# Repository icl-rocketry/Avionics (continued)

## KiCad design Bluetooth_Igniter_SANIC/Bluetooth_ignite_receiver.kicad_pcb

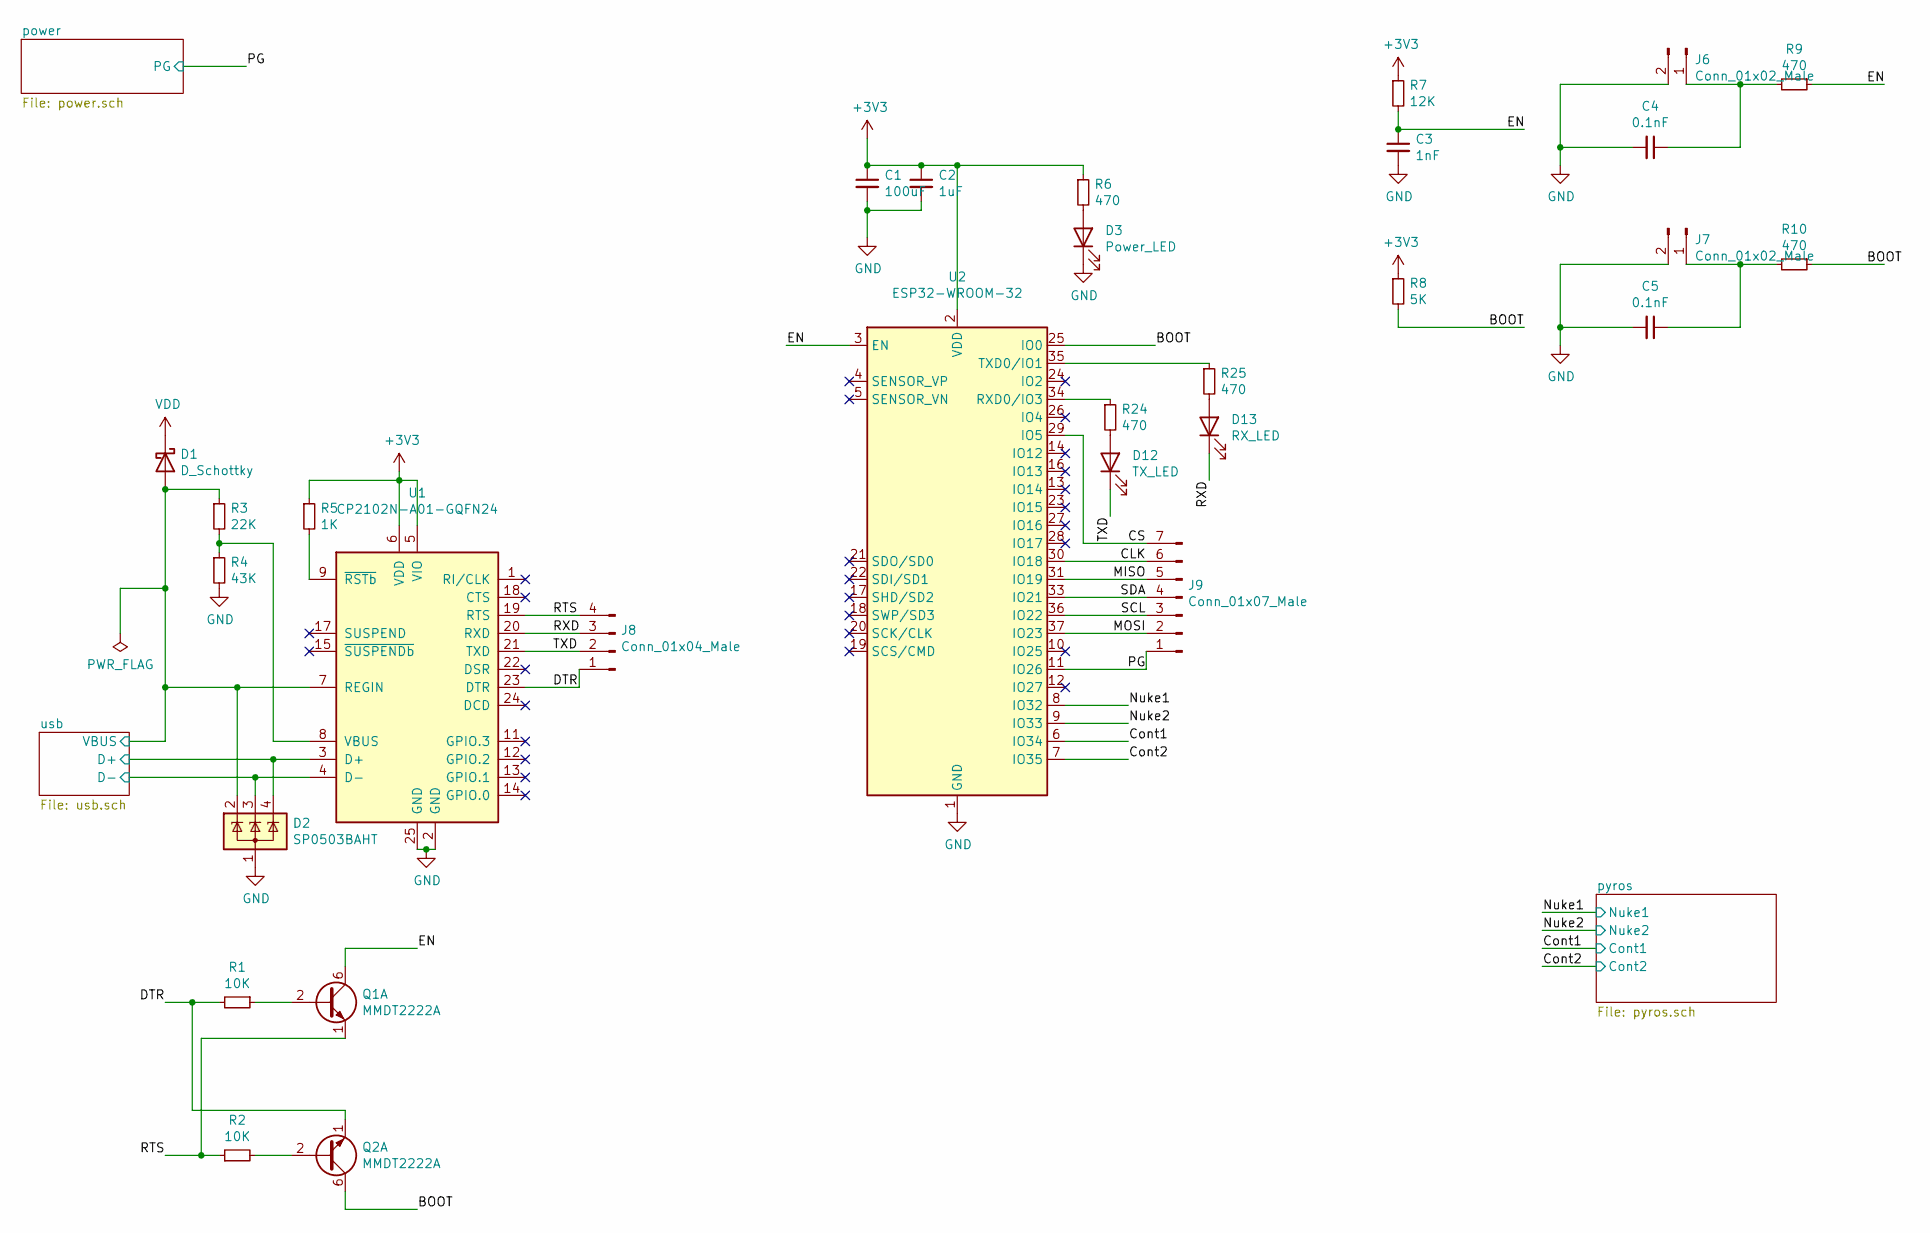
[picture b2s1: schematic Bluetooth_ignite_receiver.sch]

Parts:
C1: 100uF; C_0603_1608Metric
C2: 1uF; C_0603_1608Metric
C3: 1nF; C_0603_1608Metric
C4, C5: 0.1nF; C_0603_1608Metric
D1: D_Schottky; D_SOD-123F
D2: SP0503BAHT; SOT-143
D3: Power_LED; LED_0603_1608Metric_Castellated
D12: TX_LED; LED_0603_1608Metric_Castellated
D13: RX_LED; LED_0603_1608Metric_Castellated
J6, J7: Conn_01x02_Male; PinHeader_1x02_P2.54mm_Vertical
J8: Conn_01x04_Male; PinHeader_1x04_P2.54mm_Vertical
J9: Conn_01x07_Male; PinHeader_1x07_P2.54mm_Vertical
Q1, Q2: MMDT2222A; SOT-363_SC-70-6
R1, R2: 10K; R_0603_1608Metric
R3: 22K; R_0603_1608Metric
R4: 43K; R_0603_1608Metric
R5: 1K; R_0603_1608Metric
R6, R9, R10, R24, R25: 470; R_0603_1608Metric
R7: 12K; R_0603_1608Metric
R8: 5K; R_0603_1608Metric
U1: CP2102N-A01-GQFN24; QFN-24-1EP_4x4mm_P0.5mm_EP2.6x2.6mm
U2: ESP32-WROOM-32

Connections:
+3V3: C1.1, C2.1, R5.1, R6.1, R7.1, R8.1, U1.5 (VIO), U1.6 (VDD), U2.2 (VDD); also elsewhere on the board
/BOOT: Q2.6 (C1), R8.2, R10.1, U2.25 (IO0)
/CLK: J9.6, U2.30 (IO18)
/CS: J9.7, U2.29 (IO5)
/Cont1: U2.6 (IO34); also elsewhere on the board
/Cont2: U2.7 (IO35); also elsewhere on the board
/DTR: J8.1, Q2.1 (E1), R1.2, U1.23 (DTR)
/EN: C3.1, Q1.6 (C1), R7.2, R9.1, U2.3 (EN)
/MISO: J9.5, U2.31 (IO19)
/MOSI: J9.2, U2.37 (IO23)
/Nuke1: U2.8 (IO32); also elsewhere on the board
/Nuke2: U2.9 (IO33); also elsewhere on the board
/PG: J9.1, U2.11 (IO26); also elsewhere on the board
/RTS: J8.4, Q1.1 (E1), R2.1, U1.19 (RTS)
/RXD: D13.1 (K), J8.3, U1.20 (RXD)
/SCL: J9.3, U2.36 (IO22)
/SDA: J9.4, U2.33 (IO21)
/TXD: D12.1 (K), J8.2, U1.21 (TXD)
/usb/D+: D2.4 (K), U1.3 (D+); also elsewhere on the board
/usb/D-: D2.3 (K), U1.4 (D-); also elsewhere on the board
/usb/VBUS: D1.2 (A), D2.2 (K), R3.1, U1.7 (REGIN); also elsewhere on the board
GND: C1.2, C2.2, C3.2, C4.2, C5.2, D2.1 (A), D3.1 (K), J6.2, J7.2, R4.2, U1.2 (GND), U1.25 (GND), U2.1 (GND), U2.15 (GND), U2.38 (GND), U2.39 (GND); also elsewhere on the board
unnamed: C4.1, J6.1, R9.2
unnamed: C5.1, J7.1, R10.2
unnamed: D3.2 (A), R6.2
unnamed: D12.2 (A), R24.2
unnamed: D13.2 (A), R25.2
unnamed: Q1.2 (B1), R1.1
unnamed: Q2.2 (B1), R2.2
unnamed: R3.2, R4.1, U1.8 (VBUS)
unnamed: R5.2, U1.9 (~RSTb)
unnamed: R24.1, U2.34 (RXD0/IO3)
unnamed: R25.1, U2.35 (TXD0/IO1)
VDD: D1.1 (K); also elsewhere on the board

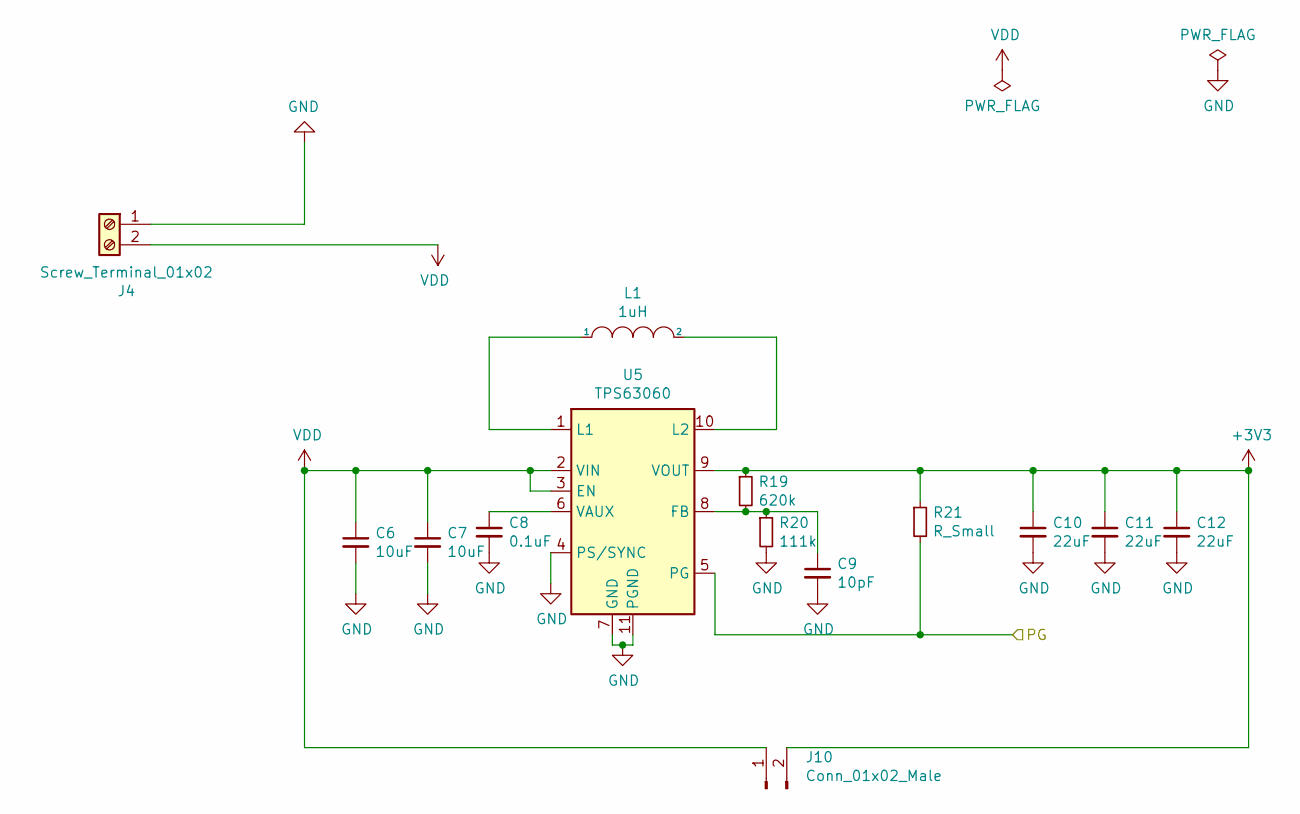
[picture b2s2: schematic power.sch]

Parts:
C6, C7: 10uF; C_0603_1608Metric
C8: 0.1uF; C_0603_1608Metric
C9: 10pF; C_0603_1608Metric
C10, C11, C12: 22uF; C_0603_1608Metric
J4: Screw_Terminal_01x02; TerminalBlock_Phoenix_PT-1,5-2-5.0-H_1x02_P5.00mm_Horizontal
J10: Conn_01x02_Male; PinHeader_1x02_P2.54mm_Vertical
L1: 1uH; L_Taiyo-Yuden_NR-30xx
R19: 620k; R_0603_1608Metric
R20: 111k; R_0603_1608Metric
R21: R_Small; R_0603_1608Metric
U5: TPS63060; Texas_S-PWSON-N10_ThermalVias

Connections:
+3V3: C10.1, C11.1, C12.1, J10.2, R19.1, R21.1, U5.9 (VOUT); also elsewhere on the board
/PG: R21.2, U5.5 (PG); also elsewhere on the board
GND: C6.2, C7.2, C8.2, C9.2, C10.2, C11.2, C12.2, J4.1, R20.2, U5.4 (PS/SYNC), U5.7 (GND), U5.11 (PGND); also elsewhere on the board
unnamed: C8.1, U5.6 (VAUX)
unnamed: C9.1, R19.2, R20.1, U5.8 (FB)
unnamed: L1.1, U5.1 (L1)
unnamed: L1.2, U5.10 (L2)
VDD: C6.1, C7.1, J4.2, J10.1, U5.2 (VIN), U5.3 (EN); also elsewhere on the board

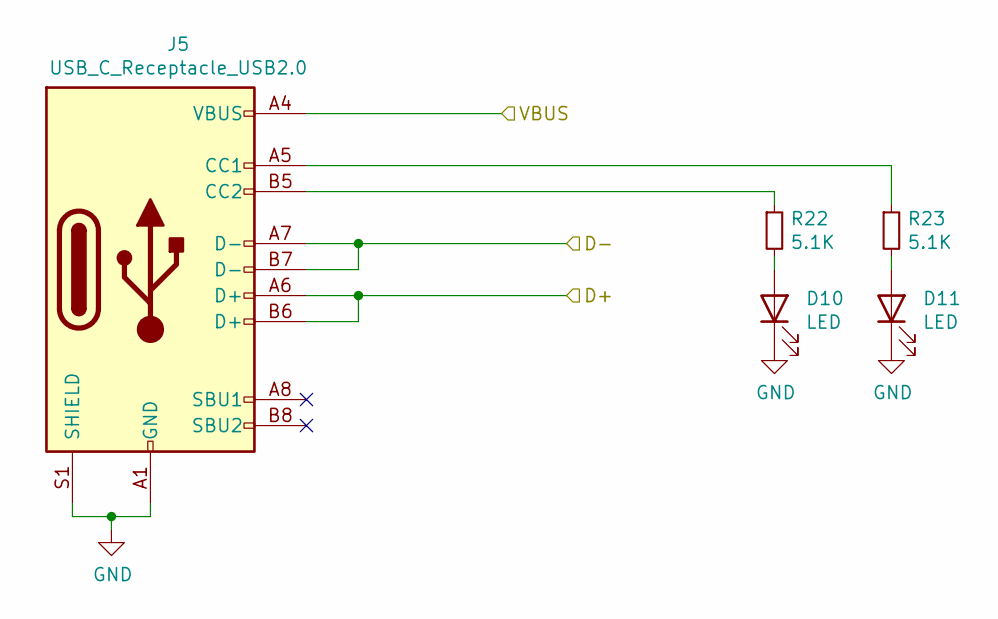
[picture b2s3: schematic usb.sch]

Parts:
D10, D11: LED; LED_0603_1608Metric_Castellated
J5: USB_C_Receptacle_USB2.0; USB_C_Receptacle_XKB_U262-16XN-4BVC11
R22, R23: 5.1K; R_0603_1608Metric

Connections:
/usb/D+: J5.A6 (D+), J5.B6 (D+); also elsewhere on the board
/usb/D-: J5.A7 (D-), J5.B7 (D-); also elsewhere on the board
/usb/VBUS: J5.A4 (VBUS), J5.A9 (VBUS), J5.B4 (VBUS), J5.B9 (VBUS); also elsewhere on the board
GND: D10.1 (K), D11.1 (K), J5.A1 (GND), J5.A12 (GND), J5.B1 (GND), J5.B12 (GND), J5.S1 (SHIELD); also elsewhere on the board
unnamed: D10.2 (A), R22.2
unnamed: D11.2 (A), R23.2
unnamed: J5.A5 (CC1), R23.1
unnamed: J5.B5 (CC2), R22.1

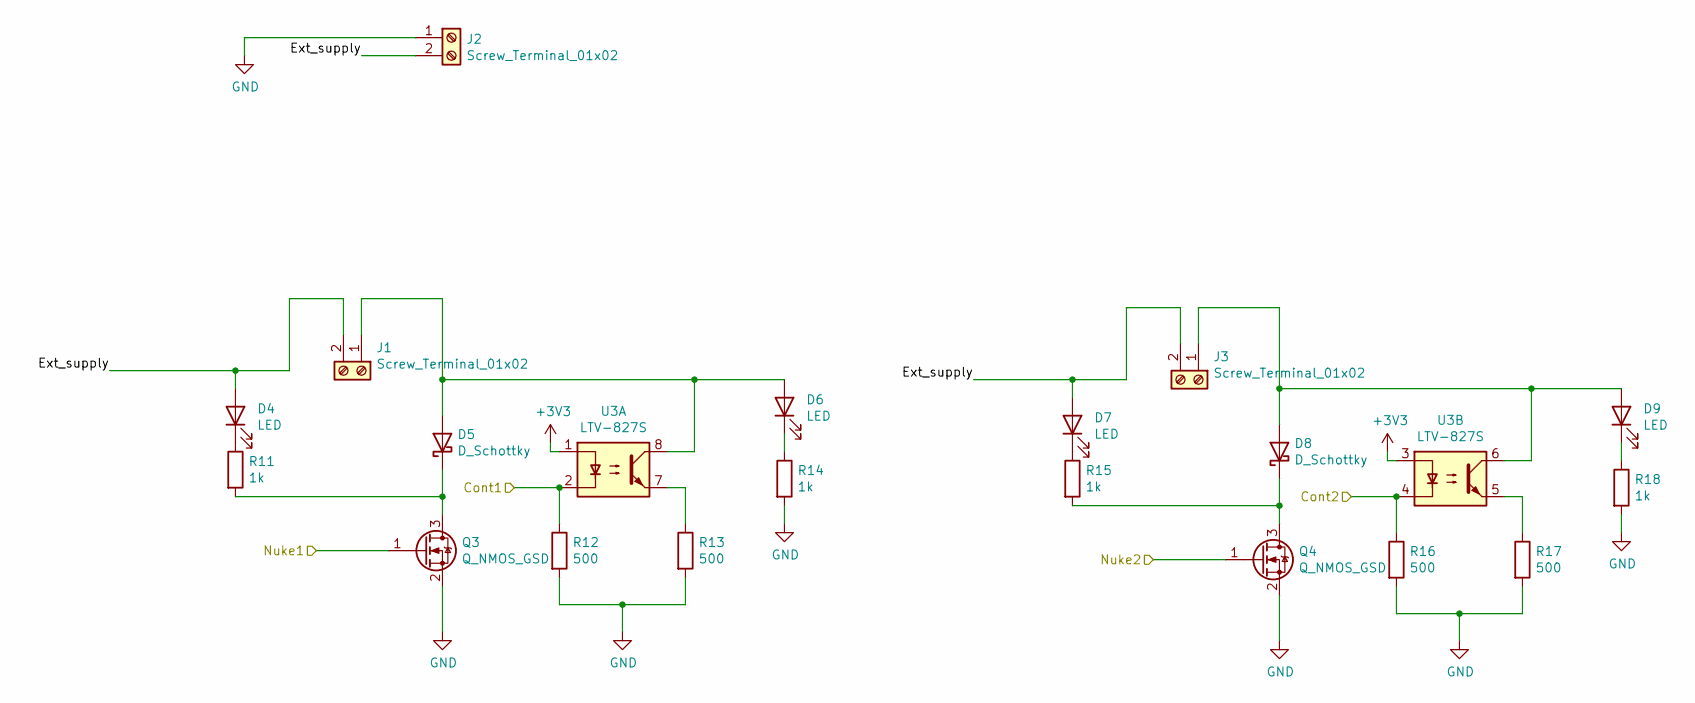
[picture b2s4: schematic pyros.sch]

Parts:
D4, D6, D7, D9: LED; LED_0603_1608Metric_Castellated
D5, D8: D_Schottky; D_SOD-123F
J1, J2, J3: Screw_Terminal_01x02; TerminalBlock_Phoenix_PT-1,5-2-5.0-H_1x02_P5.00mm_Horizontal
Q3, Q4: Q_NMOS_GSD; SOT-23
R11, R14, R15, R18: 1k; R_0603_1608Metric
R12, R13, R16, R17: 500; R_0603_1608Metric
U3: LTV-827S; SMDIP-8_W9.53mm

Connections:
+3V3: U3.1, U3.3; also elsewhere on the board
/Cont1: R12.1, U3.2; also elsewhere on the board
/Cont2: R16.1, U3.4; also elsewhere on the board
/Nuke1: Q3.1 (G); also elsewhere on the board
/Nuke2: Q4.1 (G); also elsewhere on the board
/pyros/Ext_supply: D4.2 (A), D7.2 (A), J1.2, J2.2, J3.2
GND: J2.1, Q3.2 (S), Q4.2 (S), R12.2, R13.2, R14.2, R16.2, R17.2, R18.2; also elsewhere on the board
unnamed: D4.1 (K), R11.1
unnamed: D5.1 (K), Q3.3 (D), R11.2
unnamed: D5.2 (A), D6.2 (A), J1.1, U3.8
unnamed: D6.1 (K), R14.1
unnamed: D7.1 (K), R15.1
unnamed: D8.1 (K), Q4.3 (D), R15.2
unnamed: D8.2 (A), D9.2 (A), J3.1, U3.6
unnamed: D9.1 (K), R18.1
unnamed: R13.1, U3.7
unnamed: R17.1, U3.5

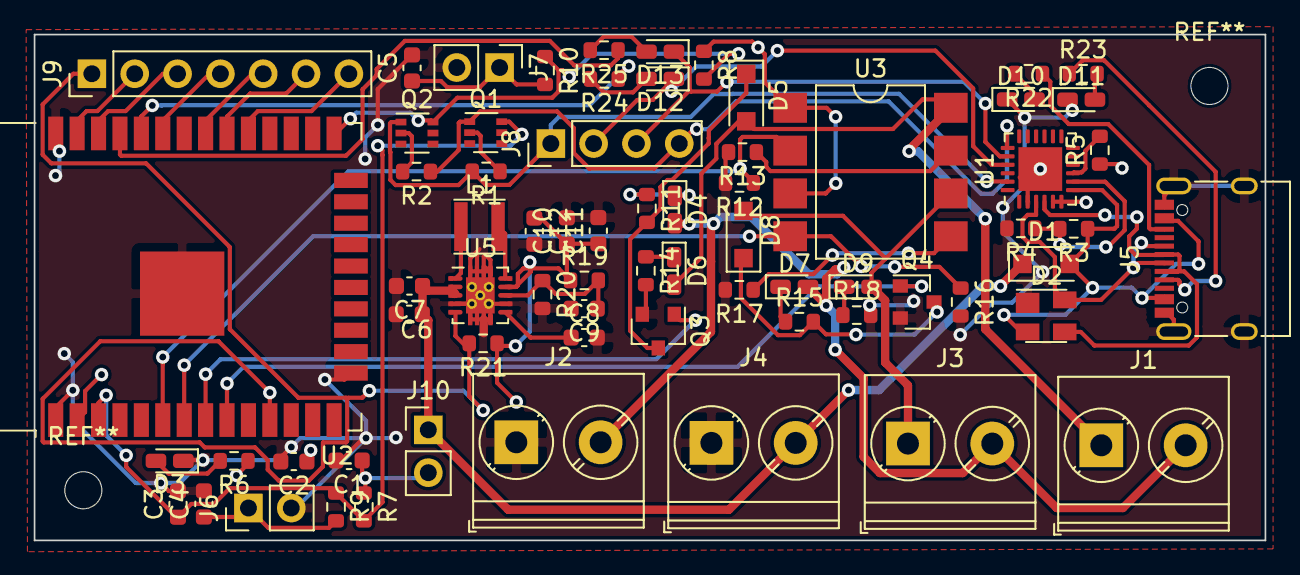
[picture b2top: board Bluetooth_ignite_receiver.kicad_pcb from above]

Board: 2 copper layers, 73.0 x 30.0 mm, 69 parts (0 on the bottom side), 53 nets.

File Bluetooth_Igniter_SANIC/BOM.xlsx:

Reference | Quantity | Value | Footprint | MPN | Price($) | Total Price | Link
C1 | 1 | 100uF | Capacitor_SMD:C_0603_1608Metric | TAJB107K006RNJ | 0.20519999999999999 | 0.20519999999999999 | https://jlcpcb.com/parts/componentSearch?isFirstLevel=true&f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
C10 C11 C12 | 3 | 22uF | Capacitor_SMD:C_0603_1608Metric | CL21A226MQQNNNE | 2.1399999999999999E-2 | 6.4199999999999993E-2 | https://jlcpcb.com/parts/componentSearch?isFirstLevel=true&f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
C2 | 1 | 1uF | Capacitor_SMD:C_0603_1608Metric | CL05A105KP5NNNC | 5.7000000000000002E-3 | 5.7000000000000002E-3 | https://jlcpcb.com/parts/componentSearch?isFirstLevel=true&f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
C3 C4 C5 | 3 | 1nF | Capacitor_SMD:C_0603_1608Metric | CL21B102KBCNNNC | 1.09E-2 | 3.27E-2 | https://jlcpcb.com/parts/componentSearch?isFirstLevel=true&f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
C6 C7 | 2 | 10uF | Capacitor_SMD:C_0603_1608Metric | CL05A106MQ5NUNC | 1.2200000000000001E-2 | 2.4400000000000002E-2 | https://jlcpcb.com/parts/componentSearch?isFirstLevel=true&f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
C8 | 1 | 0.1uF | Capacitor_SMD:C_0603_1608Metric |  |  | 0
C9 | 1 | 10pF | Capacitor_SMD:C_0603_1608Metric |  |  | 0
D1 D5 D8 | 3 | D_Schottky | Diode_SMD:D_SOD-123F |  |  | 0
D4 D6 D7 D9 D10 D11 | 6 | LED | LED_SMD:LED_0603_1608Metric_Castellated |  |  | 0
D12 | 1 | TX_LED | LED_SMD:LED_0603_1608Metric_Castellated |  |  | 0
D13 | 1 | RX_LED | LED_SMD:LED_0603_1608Metric_Castellated |  |  | 0
D2 | 1 | SP0503BAHT | Package_TO_SOT_SMD:SOT-143 |  |  | 0
D3 | 1 | Power_LED | LED_SMD:LED_0603_1608Metric_Castellated |  |  | 0
J1 J2 J3 J4 | 4 | Screw_Terminal_01x02 | TerminalBlock_Phoenix:TerminalBlock_Phoenix_PT-1,5-2-5.0-H_1x02_P5.00mm_Horizon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 |  |  | 0
J5 | 1 | USB_C_Receptacle_USB2.0 | Connector_USB:USB_C_Receptacle_XKB_U262-16XN-4BVC11 |  |  | 0
J6 J7 J10 | 3 | Conn_01x02_Male | Connector_PinHeader_2.54mm:PinHeader_1x02_P2.54mm_Vertical |  |  | 0
J8 | 1 | Conn_01x04_Male | Connector_PinHeader_2.54mm:PinHeader_1x04_P2.54mm_Vertical |  |  | 0
J9 | 1 | Conn_01x07_Male | Connector_PinHeader_2.54mm:PinHeader_1x07_P2.54mm_Vertical |  |  | 0
L1 | 1 | 1uH | Inductor_SMD:L_Taiyo-Yuden_NR-30xx |  |  | 0
Q1 Q2 | 2 | MMDT2222A | Package_TO_SOT_SMD:SOT-363_SC-70-6 |  |  | 0
Q3 Q4 | 2 | Q_NMOS_GSD | Package_TO_SOT_SMD:SOT-23 |  |  | 0
R1 R2 | 2 | 10K | Resistor_SMD:R_0603_1608Metric |  |  | 0
R11 R14 R15 R18 | 4 | 1k | Resistor_SMD:R_0603_1608Metric |  |  | 0
R12 R13 R16 R17 | 4 | 500 | Resistor_SMD:R_0603_1608Metric |  |  | 0
R19 | 1 | 620k | Resistor_SMD:R_0603_1608Metric |  |  | 0
R20 | 1 | 111k | Resistor_SMD:R_0603_1608Metric |  |  | 0
R21 | 1 | R_Small | Resistor_SMD:R_0603_1608Metric |  |  | 0
R22 R23 | 2 | 5.1K | Resistor_SMD:R_0603_1608Metric |  |  | 0
R3 | 1 | 22K | Resistor_SMD:R_0603_1608Metric |  |  | 0
R4 | 1 | 43K | Resistor_SMD:R_0603_1608Metric |  |  | 0
R5 | 1 | 1K | Resistor_SMD:R_0603_1608Metric |  |  | 0
R6 R9 R10 R24 R25 | 5 | 470 | Resistor_SMD:R_0603_1608Metric |  |  | 0
R7 | 1 | 12K | Resistor_SMD:R_0603_1608Metric |  |  | 0
R8 | 1 | 5K | Resistor_SMD:R_0603_1608Metric |  |  | 0
U1 | 1 | CP2102N-A01-GQFN24 | Package_DFN_QFN:QFN-24-1EP_4x4mm_P0.5mm_EP2.6x2.6mm |  |  | 0
U2 | 1 | ESP32-WROOM-32 | RF_Module:ESP32-WROOM-32 |  |  | 0
U3 | 1 | LTV-827S | Package_DIP:SMDIP-8_W9.53mm |  |  | 0
U5 | 1 | TPS63060 | Package_SON:Texas_S-PWSON-N10_ThermalVias |  |  | 0

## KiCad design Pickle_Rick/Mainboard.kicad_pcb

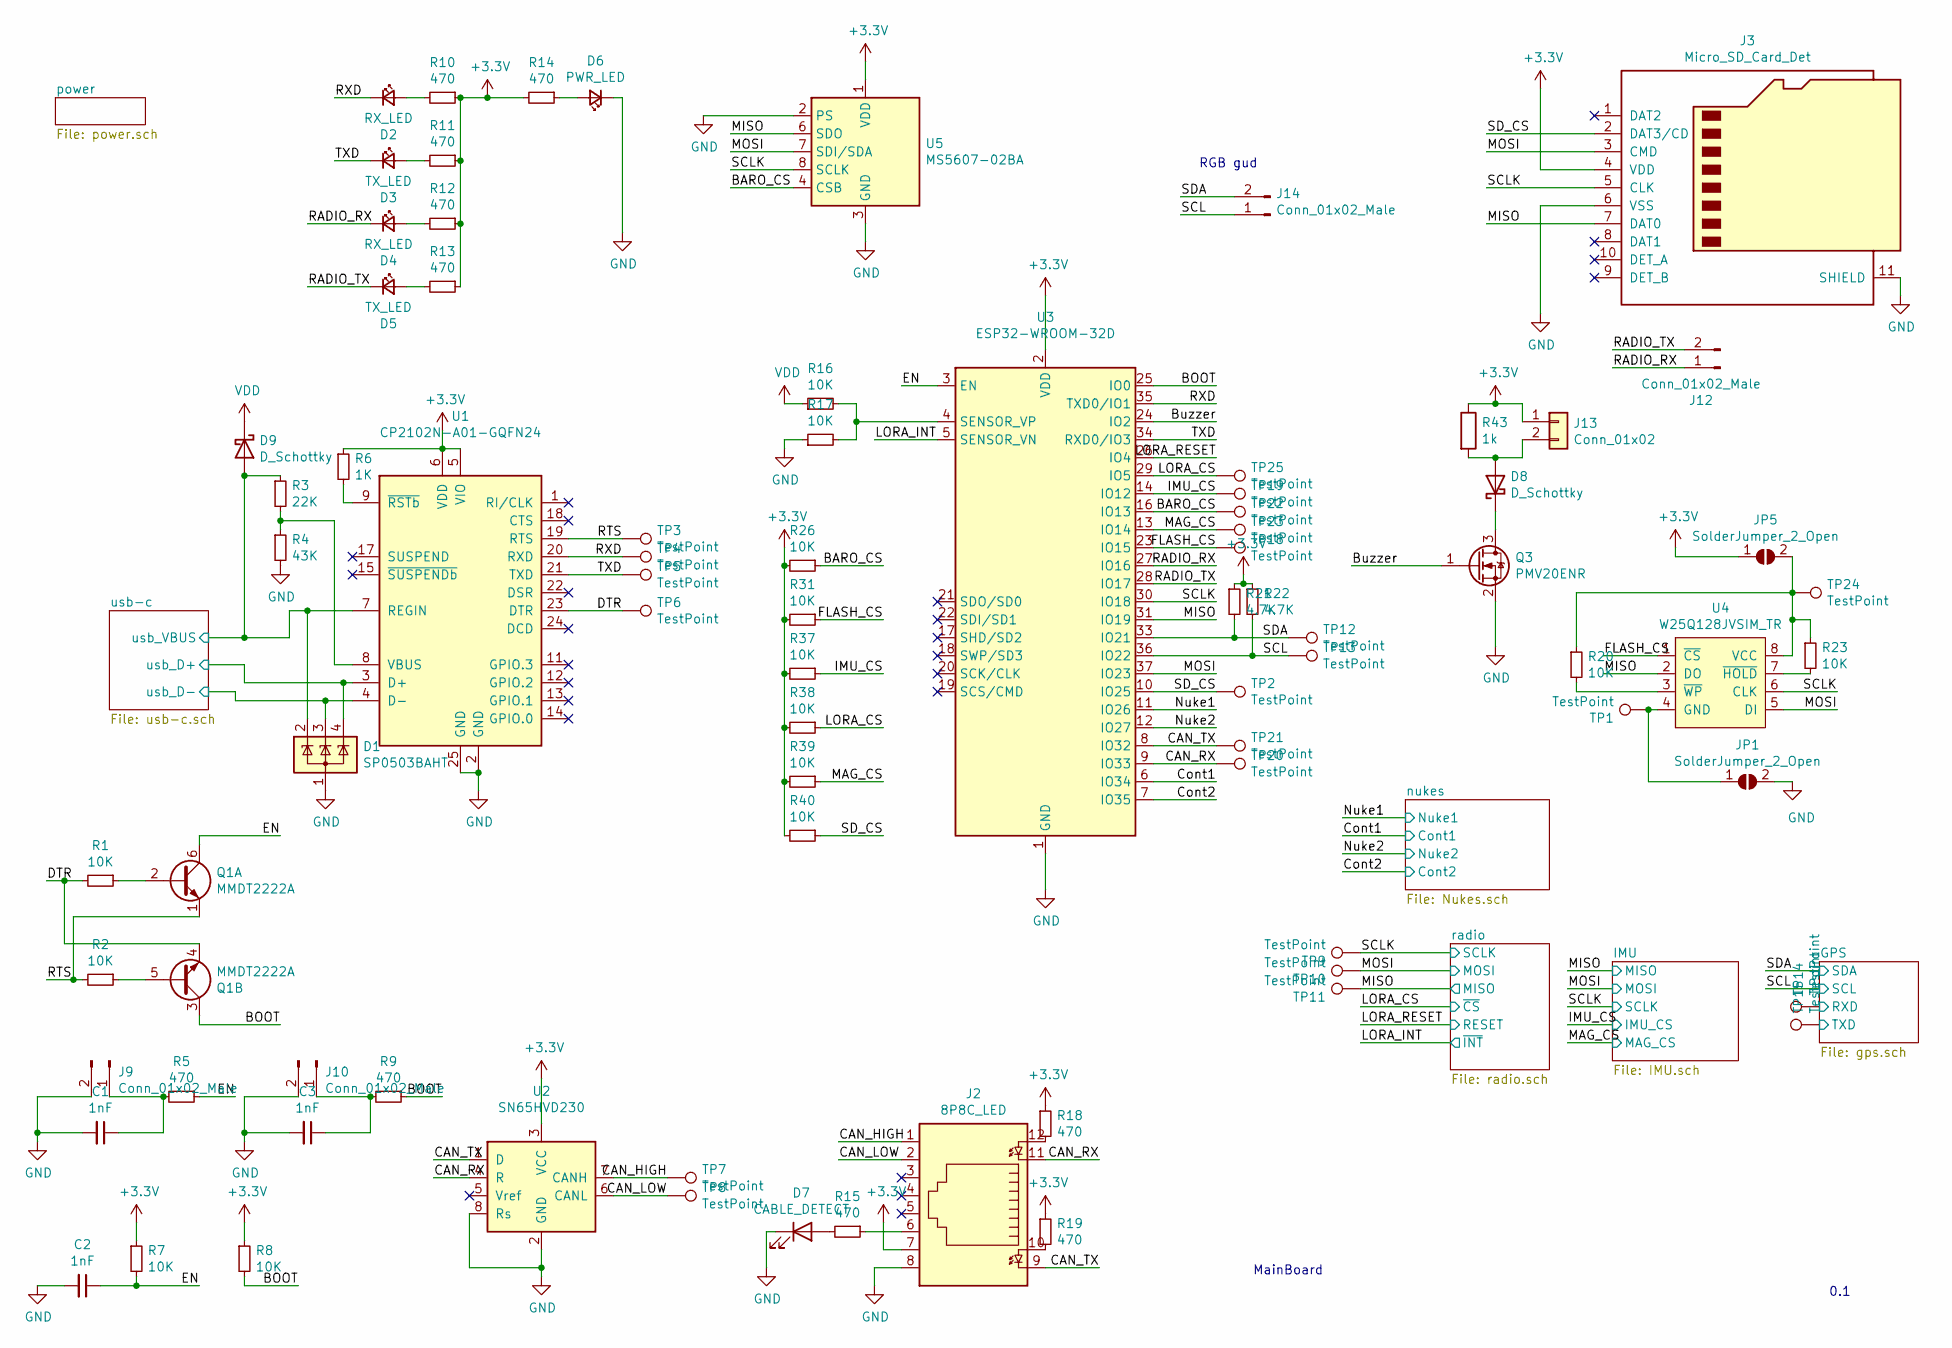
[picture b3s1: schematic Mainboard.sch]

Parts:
C1, C2, C3: 1nF; C_0603_1608Metric
D1: SP0503BAHT; SOT-143
D2, D4: RX_LED; LED_0603_1608Metric_Castellated
D3, D5: TX_LED; LED_0603_1608Metric_Castellated
D6: PWR_LED; LED_0603_1608Metric_Castellated
D7: CABLE_DETECT; LED_0603_1608Metric_Castellated
D8, D9: D_Schottky; D_SOD-123F
J2: 8P8C_LED; RJ45_Amphenol_RJHSE538X
J3: Micro_SD_Card_Det; microSD_HC_Hirose_DM3AT-SF-PEJM5
J9, J10, J12, J14: Conn_01x02_Male; PinHeader_1x02_P2.54mm_Vertical
J13: Conn_01x02; JST_XH_B2B-XH-A_1x02_P2.50mm_Vertical
JP1, JP5: SolderJumper_2_Open; SolderJumper-2_P1.3mm_Open_TrianglePad1.0x1.5mm
Q1: MMDT2222A; SOT-363_SC-70-6
Q3: PMV20ENR; SOT-23
R1, R2, R7, R8, R16, R17, R20, R23, R26, R31, R37, R38, R39, R40: 10K; R_0603_1608Metric
R3: 22K; R_0603_1608Metric
R4: 43K; R_0603_1608Metric
R5, R9, R10, R11, R12, R13, R14, R15, R18, R19: 470; R_0603_1608Metric
R6: 1K; R_0603_1608Metric
R21, R22: 4.7K; R_0603_1608Metric
R43: 1k; R_0603_1608Metric
TP1, TP2, TP3, TP4, TP5, TP6, TP7, TP8, TP9, TP10, TP11, TP12, TP13, TP14, TP15, TP18, TP19, TP20, TP21, TP22, TP23, TP24, TP25: TestPoint; TestPoint_THTPad_1.0x1.0mm_Drill0.5mm
U1: CP2102N-A01-GQFN24; QFN-24-1EP_4x4mm_P0.5mm_EP2.6x2.6mm_ThermalVias
U2: SN65HVD230; SOIC-8_3.9x4.9mm_P1.27mm
U3: ESP32-WROOM-32D; ESP32-WROOM-32
U4: W25Q128JVSIM_TR; SOIC-8_5.275x5.275mm_P1.27mm
U5: MS5607-02BA; LGA-8_3x5mm_P1.25mm

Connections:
/BARO_CS: R26.1, TP22.1, U3.16 (IO13), U5.4 (CSB), U5.5 (CSB)
/BOOT: Q1.3 (C2), R8.2, R9.1, U3.25 (IO0)
/Buzzer: Q3.1 (G), U3.24 (IO2)
/CAN_HIGH: J2.1, TP7.1, U2.7 (CANH)
/CAN_LOW: J2.2, TP8.1, U2.6 (CANL)
/CAN_RX: J2.11, TP20.1, U2.4 (R), U3.9 (IO33)
/CAN_TX: J2.9, TP21.1, U2.1 (D), U3.8 (IO32)
/Cont1: U3.6 (IO34); also elsewhere on the board
/Cont2: U3.7 (IO35); also elsewhere on the board
/DTR: Q1.4 (E2), R1.2, TP6.1, U1.23 (DTR)
/EN: C2.1, Q1.6 (C1), R5.1, R7.2, U3.3 (EN)
/FLASH_CS: R31.1, TP18.1, U3.23 (IO15), U4.1 (~CS)
/GPS/RXD: TP14.1; also elsewhere on the board
/GPS/TXD: TP15.1; also elsewhere on the board
/IMU_CS: R37.1, TP19.1, U3.14 (IO12); also elsewhere on the board
/LORA_CS: R38.1, TP25.1, U3.29 (IO5); also elsewhere on the board
/LORA_INT: U3.5 (SENSOR_VN); also elsewhere on the board
/LORA_RESET: U3.26 (IO4); also elsewhere on the board
/MAG_CS: R39.1, TP23.1, U3.13 (IO14); also elsewhere on the board
/MISO: J3.7 (DAT0), TP11.1, U3.31 (IO19), U4.2 (DO), U5.6 (SDO); also elsewhere on the board
/MOSI: J3.3 (CMD), TP10.1, U3.37 (IO23), U4.5 (DI), U5.7 (SDI/SDA); also elsewhere on the board
/Nuke1: U3.11 (IO26); also elsewhere on the board
/Nuke2: U3.12 (IO27); also elsewhere on the board
/RADIO_RX: D4.1 (K), J12.1, U3.27 (IO16)
/RADIO_TX: D5.1 (K), J12.2, U3.28 (IO17)
/RTS: Q1.1 (E1), R2.2, TP3.1, U1.19 (RTS)
/RXD: D2.1 (K), TP4.1, U1.20 (RXD), U3.35 (TXD0/IO1)
/SCL: J14.1, R22.2, TP13.1, U3.36 (IO22); also elsewhere on the board
/SCLK: J3.5 (CLK), TP9.1, U3.30 (IO18), U4.6 (CLK), U5.8 (SCLK); also elsewhere on the board
/SDA: J14.2, R21.2, TP12.1, U3.33 (IO21); also elsewhere on the board
/SD_CS: J3.2 (DAT3/CD), R40.1, TP2.1, U3.10 (IO25)
/TXD: D3.1 (K), TP5.1, U1.21 (TXD), U3.34 (RXD0/IO3)
/usb-c/usb_D+: D1.4 (K), U1.3 (D+); also elsewhere on the board
/usb-c/usb_D-: D1.3 (K), U1.4 (D-); also elsewhere on the board
/usb-c/usb_VBUS: D1.2 (K), D9.2 (A), R3.1, U1.7 (REGIN); also elsewhere on the board
GND: C1.2, C2.2, C3.2, D1.1 (A), D6.1 (K), D7.1 (K), J2.8, J3.6 (VSS), J3.11 (SHIELD), J9.2, J10.2, JP1.2 (B), Q3.2 (S), R4.2, R17.1, U1.2 (GND), U1.25 (GND), U2.2 (GND), U2.8 (Rs), U3.1 (GND), U3.15 (GND), U3.38 (GND), U3.39 (GND), U5.2 (PS), U5.3 (GND); also elsewhere on the board
unnamed: C1.1, J9.1, R5.2
unnamed: C3.1, J10.1, R9.2
unnamed: D2.2 (A), R10.2
unnamed: D3.2 (A), R11.2
unnamed: D4.2 (A), R12.2
unnamed: D5.2 (A), R13.2
unnamed: D6.2 (A), R14.1
unnamed: D7.2 (A), R15.2
unnamed: D8.1 (K), Q3.3 (D)
unnamed: D8.2 (A), J13.2, R43.2
unnamed: J2.6, R15.1
unnamed: J2.10, R19.2
unnamed: J2.12, R18.2
unnamed: JP1.1 (A), TP1.1, U4.4 (GND)
unnamed: JP5.2 (B), R20.1, R23.1, TP24.1, U4.8 (VCC)
unnamed: Q1.2 (B1), R1.1
unnamed: Q1.5 (B2), R2.1
unnamed: R3.2, R4.1, U1.8 (VBUS)
unnamed: R6.2, U1.9 (~RSTb)
unnamed: R16.2, R17.2, U3.4 (SENSOR_VP)
unnamed: R20.2, U4.3 (~WP)
unnamed: R23.2, U4.7 (~HOLD)
VDD: D9.1 (K), R16.1; also elsewhere on the board

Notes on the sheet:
MainBoard
0.1
RGB gud

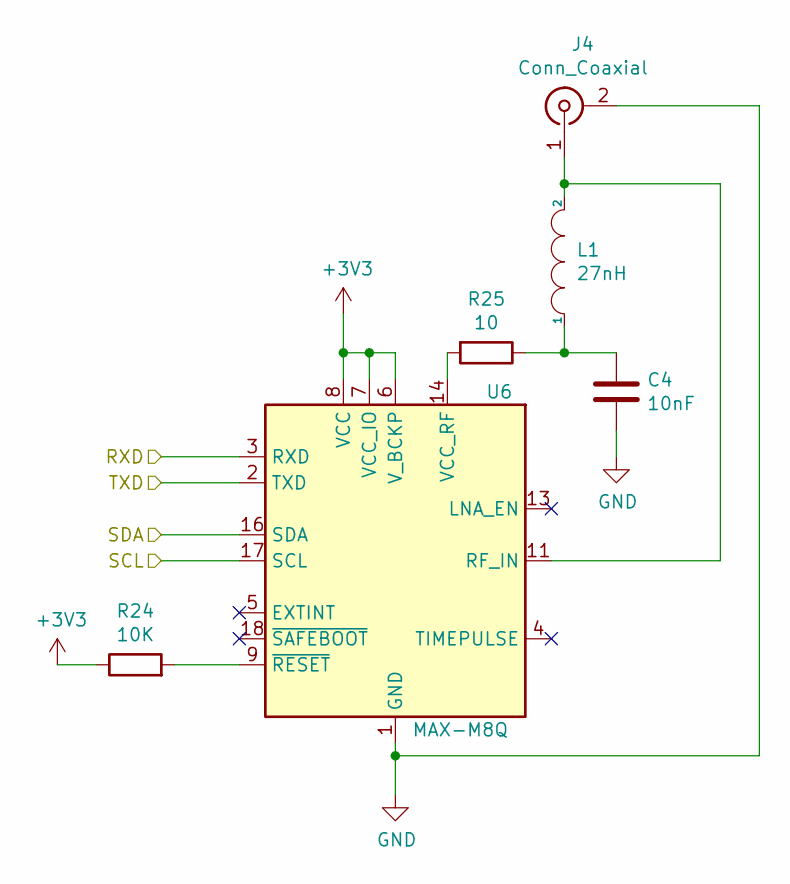
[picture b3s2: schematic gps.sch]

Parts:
C4: 10nF; C_0603_1608Metric
J4: Conn_Coaxial; U.FL_Hirose_U.FL-R-SMT-1_Vertical
L1: 27nH; L_0603_1608Metric
R24: 10K; R_0603_1608Metric
R25: 10; R_0603_1608Metric
U6: MAX-M8Q; ublox_MAX

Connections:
/GPS/RXD: U6.3 (RXD); also elsewhere on the board
/GPS/TXD: U6.2 (TXD); also elsewhere on the board
/SCL: U6.17 (SCL); also elsewhere on the board
/SDA: U6.16 (SDA); also elsewhere on the board
GND: C4.2, J4.2 (Ext), U6.1 (GND), U6.10 (GND), U6.12 (GND); also elsewhere on the board
unnamed: C4.1, L1.1, R25.1
unnamed: J4.1 (In), L1.2, U6.11 (RF_IN)
unnamed: R24.2, U6.9 (~RESET)
unnamed: R25.2, U6.14 (VCC_RF)

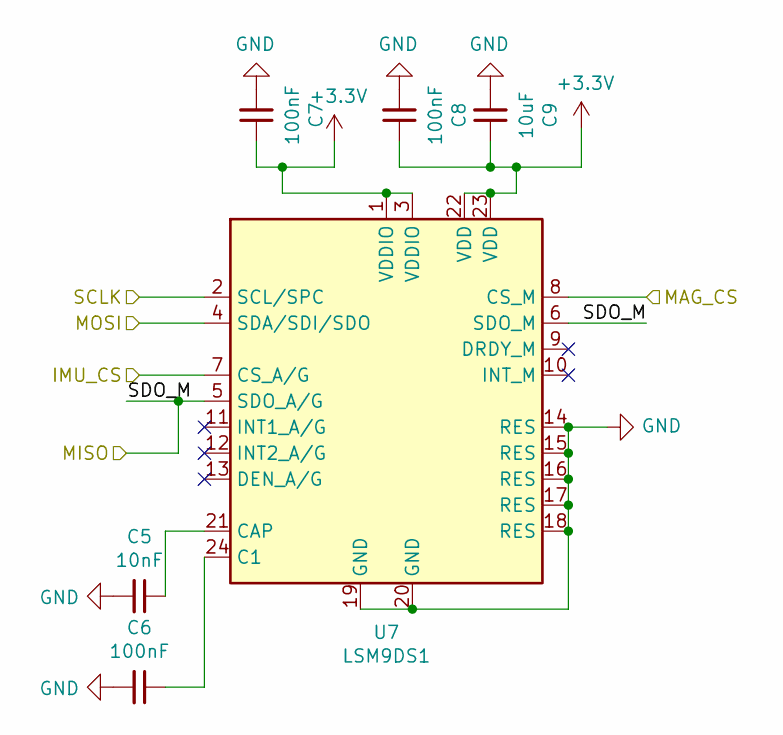
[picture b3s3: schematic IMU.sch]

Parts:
C5: 10nF; C_0603_1608Metric
C6, C7, C8: 100nF; C_0603_1608Metric
C9: 10uF; C_0603_1608Metric
U7: LSM9DS1; LGA-24L_3x3.5mm_P0.43mm

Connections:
/IMU_CS: U7.7 (CS_A/G); also elsewhere on the board
/MAG_CS: U7.8 (CS_M); also elsewhere on the board
/MISO: U7.5 (SDO_A/G), U7.6 (SDO_M); also elsewhere on the board
/MOSI: U7.4 (SDA/SDI/SDO); also elsewhere on the board
/SCLK: U7.2 (SCL/SPC); also elsewhere on the board
GND: C5.2, C6.2, C7.2, C8.2, C9.2, U7.14 (RES), U7.15 (RES), U7.16 (RES), U7.17 (RES), U7.18 (RES), U7.19 (GND), U7.20 (GND); also elsewhere on the board
unnamed: C5.1, U7.21 (CAP)
unnamed: C6.1, U7.24 (C1)

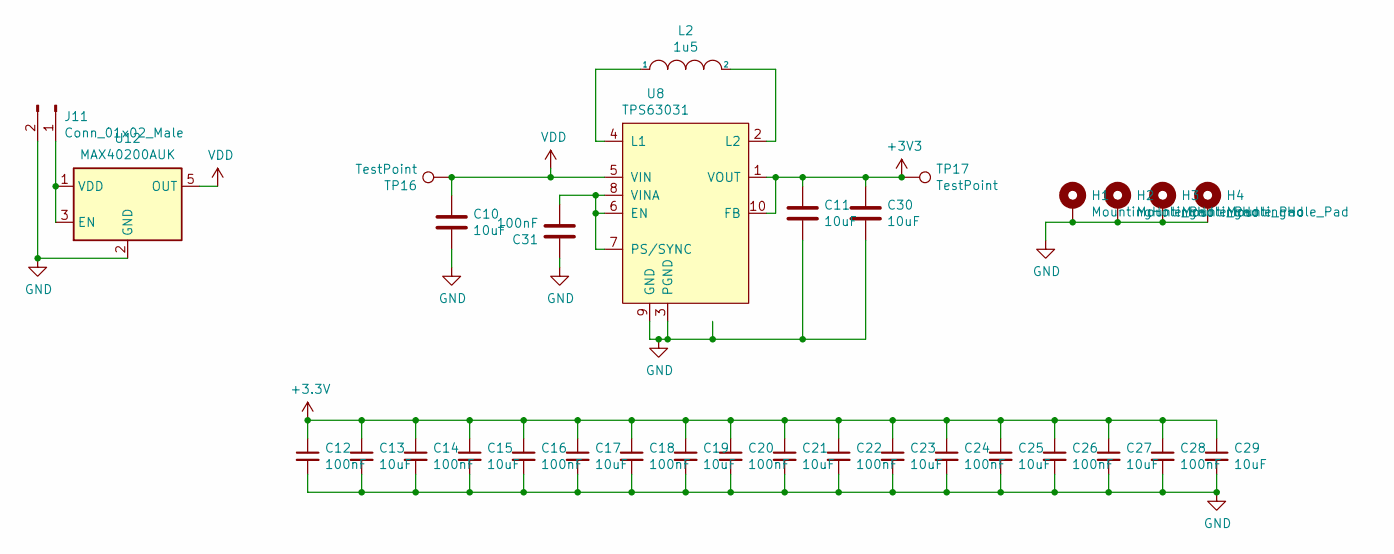
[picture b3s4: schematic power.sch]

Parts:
C10, C11, C13, C15, C17, C19, C21, C23, C25, C27, C29, C30: 10uF; C_0603_1608Metric
C12, C14, C16, C18, C20, C22, C24, C26, C28, C31: 100nF; C_0603_1608Metric
H1, H2, H3, H4: MountingHole_Pad; MountingHole_3.2mm_M3_DIN965_Pad
J11: Conn_01x02_Male; JST_PH_S2B-PH-K_1x02_P2.00mm_Horizontal
L2: 1u5; L_Taiyo-Yuden_NR-30xx
TP16, TP17: TestPoint; TestPoint_THTPad_1.0x1.0mm_Drill0.5mm
U8: TPS63031; VSON-10-1EP_2.5x2.5mm_Pitch0.5mm_ThermalPad
U12: MAX40200AUK; SOT-23-5

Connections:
GND: C10.2, C11.2, C12.2, C13.2, C14.2, C15.2, C16.2, C17.2, C18.2, C19.2, C20.2, C21.2, C22.2, C23.2, C24.2, C25.2, C26.2, C27.2, C28.2, C29.2, C30.2, C31.1, H1.1, H2.1, H3.1, H4.1, J11.2, U8.3 (PGND), U8.9 (GND), U12.2 (GND); also elsewhere on the board
unnamed: C31.2, U8.6 (EN), U8.7 (PS/SYNC), U8.8 (VINA)
unnamed: J11.1, U12.1 (VDD), U12.3 (EN)
unnamed: L2.1, U8.4 (L1)
unnamed: L2.2, U8.2 (L2)
VDD: C10.1, TP16.1, U8.5 (VIN), U12.5 (OUT); also elsewhere on the board

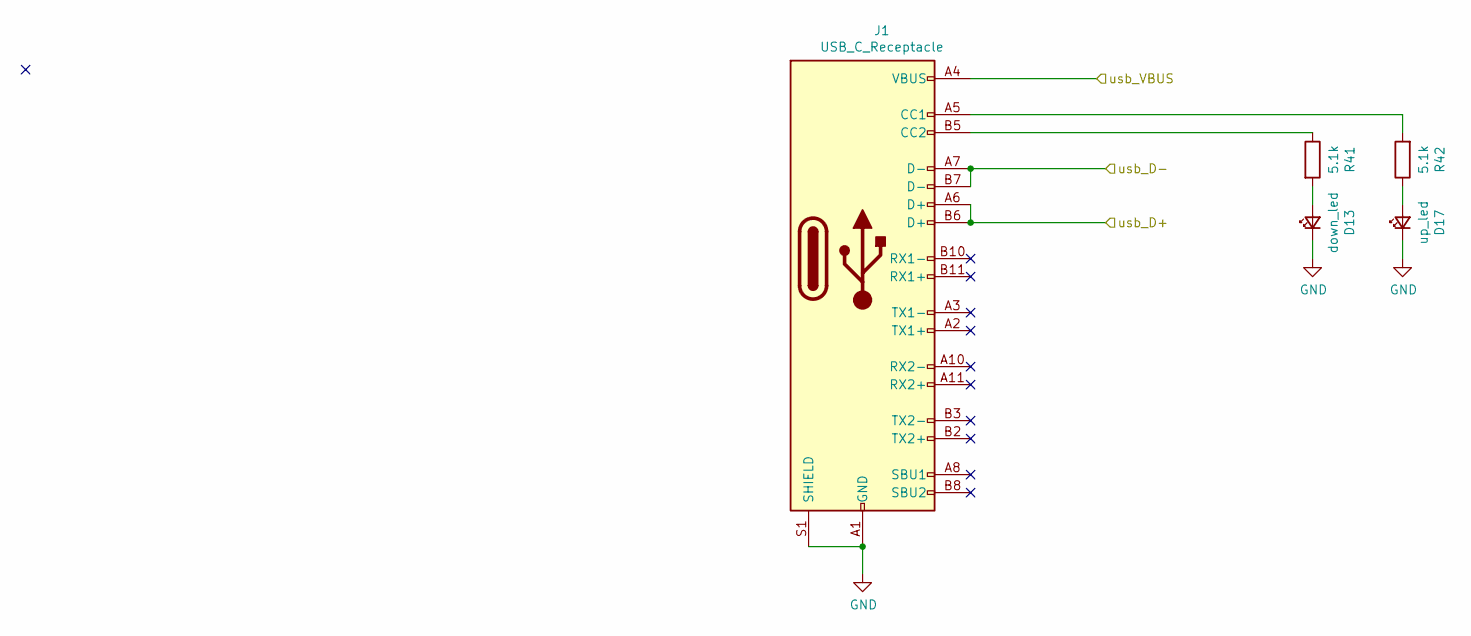
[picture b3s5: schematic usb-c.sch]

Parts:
D13: down_led; LED_0603_1608Metric_Castellated
D17: up_led; LED_0603_1608Metric_Castellated
J1: USB_C_Receptacle; USB_C_Receptacle_Amphenol_12401548E4-2A
R41, R42: 5.1k; R_0603_1608Metric

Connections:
/usb-c/usb_D+: J1.A6 (D+), J1.B6 (D+); also elsewhere on the board
/usb-c/usb_D-: J1.A7 (D-), J1.B7 (D-); also elsewhere on the board
/usb-c/usb_VBUS: J1.A4 (VBUS), J1.A9 (VBUS), J1.B4 (VBUS), J1.B9 (VBUS); also elsewhere on the board
GND: D13.1 (K), D17.1 (K), J1.A1 (GND), J1.A12 (GND), J1.B1 (GND), J1.B12 (GND), J1.S1 (SHIELD); also elsewhere on the board
unnamed: D13.2 (A), R41.2
unnamed: D17.2 (A), R42.1
unnamed: J1.A5 (CC1), R42.2
unnamed: J1.B5 (CC2), R41.1

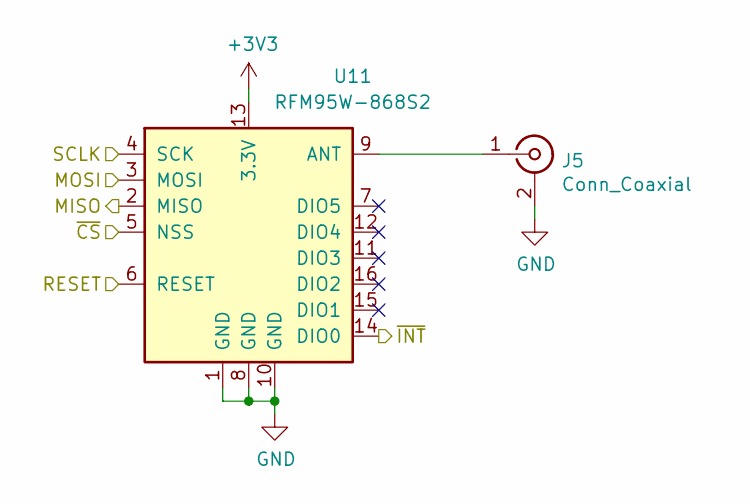
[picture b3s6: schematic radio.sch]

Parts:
J5: Conn_Coaxial; U.FL_Hirose_U.FL-R-SMT-1_Vertical
U11: RFM95W-868S2; HOPERF_RFM9XW_SMD

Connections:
/LORA_CS: U11.5 (NSS); also elsewhere on the board
/LORA_INT: U11.14 (DIO0); also elsewhere on the board
/LORA_RESET: U11.6 (RESET); also elsewhere on the board
/MISO: U11.2 (MISO); also elsewhere on the board
/MOSI: U11.3 (MOSI); also elsewhere on the board
/SCLK: U11.4 (SCK); also elsewhere on the board
GND: J5.2 (Ext), U11.1 (GND), U11.8 (GND), U11.10 (GND); also elsewhere on the board
unnamed: J5.1 (In), U11.9 (ANT)
